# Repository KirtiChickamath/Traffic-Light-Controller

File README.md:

# Traffic-Light-Controller
Microcontroller-based traffic light controller PCB using ATmega328P, RGB LEDs, and a two-digit countdown timer with SSDs. Includes onboard 12V to 5V power regulation using LM7805. Designed as the final project for a PCB design course.

## Project Details

**Project Name:** Traffic Light Controller

**Software Used:** Eagle

## Project Description

Designed a microcontroller-based traffic signal controller PCB featuring:

- **ATmega328P** as the microcontroller
- **RGB LEDs** as traffic lights (Red, Yellow, Green)
- Two **7-segment displays (SSD)** with driver ICs to show a two-digit countdown timer
- Power supply section converting **12V DC to 5V DC** using an **LM7805 voltage regulator**
- Complete **schematic and PCB layout** created using provided component libraries

The controller manages traffic signals and displays a countdown timer to indicate the remaining time for each light.

## Block Diagram

*Block diagram showing the overall system architecture*

## Schematic

## PCB Layout

## Manufacturing Tab

## Features

- Microcontroller-controlled traffic lights using RGB LEDs
- Two-digit countdown timer visible on SSDs
- On board 12V to 5V regulated power supply using LM7805

## Tools and Components

- **Microcontroller:** ATmega328P
- **Display:** Two 7-segment displays with driver ICs
- **Traffic Light:** RGB LEDs
- **Power Supply:** LM7805 voltage regulator (12V to 5V)
- Component libraries provided by the course mentor

## Project Files

- `Schematic` — Circuit diagrams  
- `PCB Layout` — PCB design layout  
- `CAM Outputs/Gerber Files` — Manufacturing files for PCB fabrication  
- `BOM` — Bill of Materials listing all components   
- `Images` — Board photos and design previews  
- `Libraries` — Libraries were provided by mentor

## Credits

This project was developed as part of a final project of a course from [Internshala](https://internshala.com/).

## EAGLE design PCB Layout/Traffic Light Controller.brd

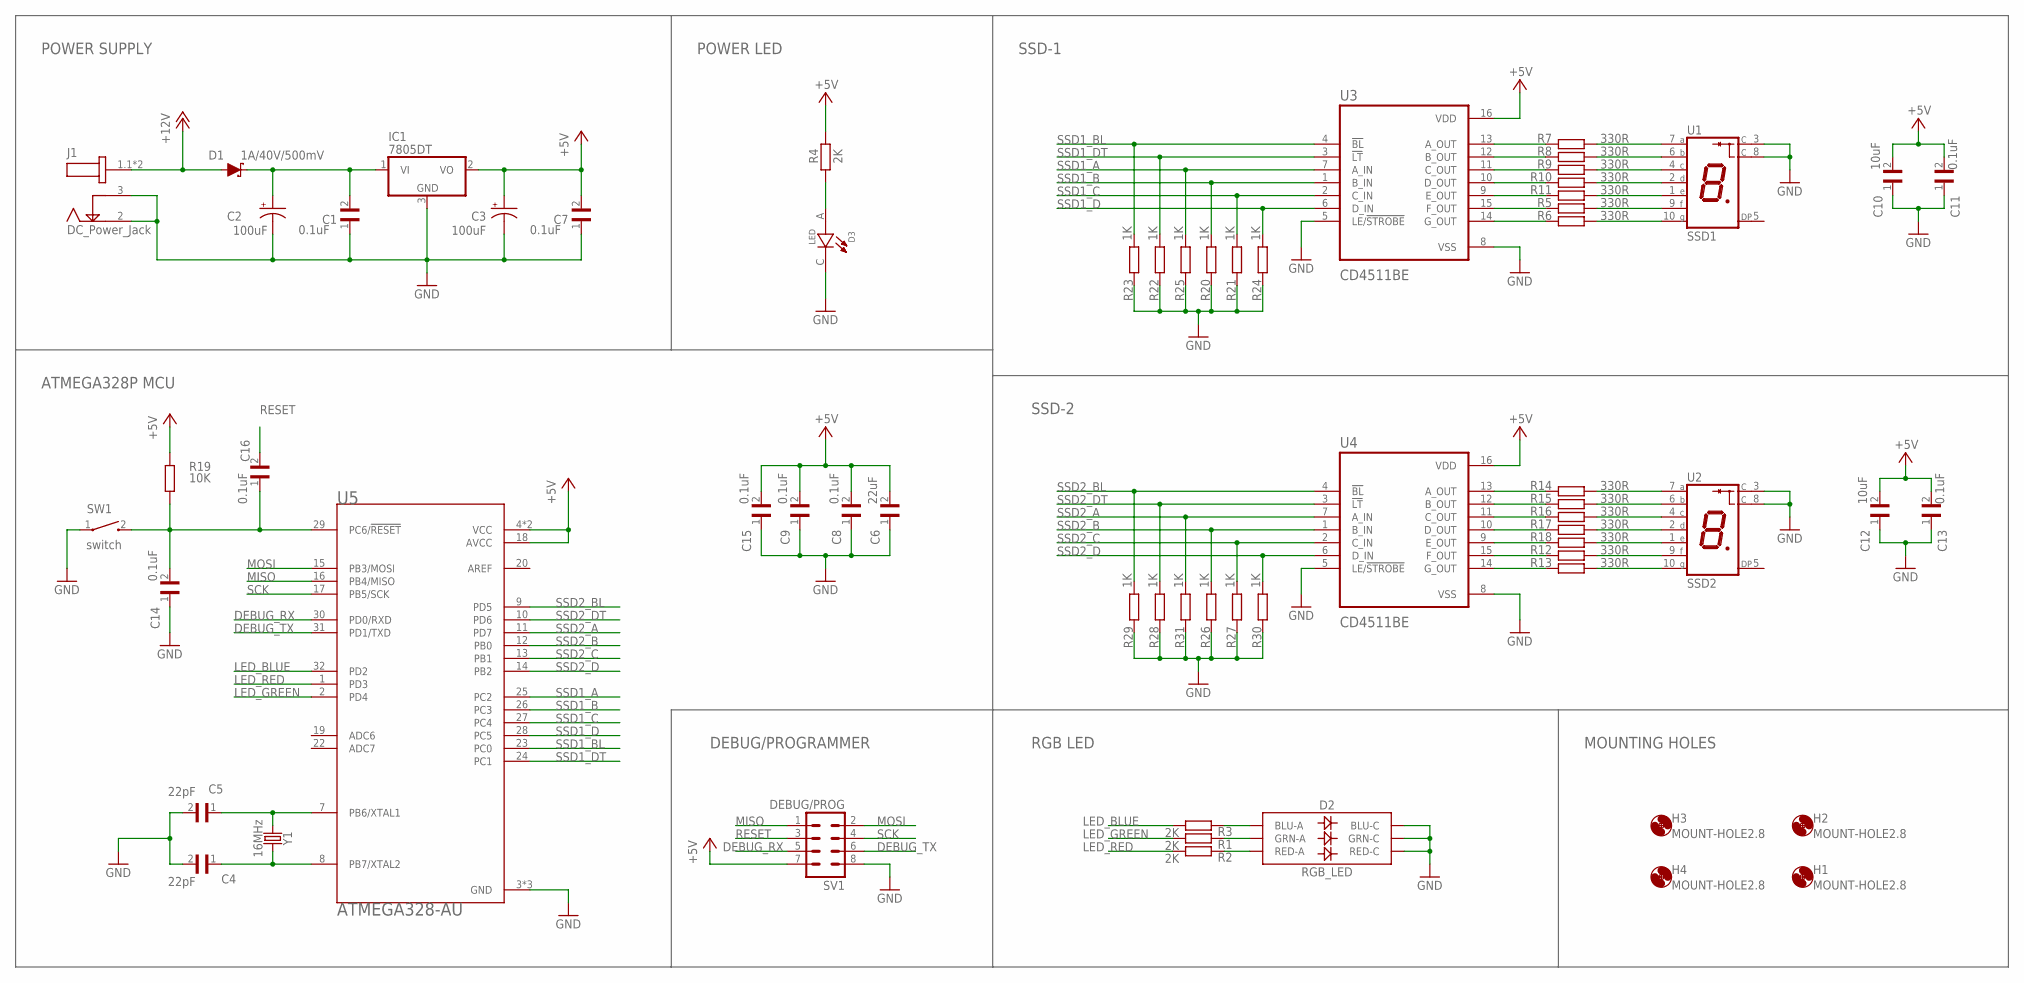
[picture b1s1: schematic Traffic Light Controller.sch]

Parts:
C1, C7, C8, C9, C11, C13, C14, C15, C16: 0.1uF; C0603
C2, C3: 100uF; CPOL-RADIAL-2.5MM-6.5MM
C4, C5: 22pF; C0603
C6: 22uF; C0603
C10, C12: 10uF; C0603
D1: 1A/40V/500mV; SMA-DIODE
D2: RGB_LED; LED-TRICOLOR-5050
D3: LED; LEDC1608X65N
H1, H2, H3, H4: MOUNT-HOLE2.8; 2,8
IC1: 7805DT; TO252
J1: DC_Power_Jack; GCT_DCJ200-05-A-XX-X_REVA
R1, R2, R3, R4: 2K; R0603
R5, R6, R7, R8, R9, R10, R11, R12, R13, R14, R15, R16, R17, R18: 330R; R0603
R19: 10K; R0603
R20, R21, R22, R23, R24, R25, R26, R27, R28, R29, R30, R31: 1K; R0603
SV1: DEBUG/PROG; MA04-2
SW1: switch; SW_1437566-3
U1: SSD1; LED_SC52-11HWA
U2: SSD2; LED_SC52-11HWA
U3, U4: CD4511BE; DIP794W45P254L1969H508Q16
U5: ATMEGA328-AU; QFP80P900X900X120-32N
Y1: 16MHz; HC49US

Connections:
+5V: C3.1 (+), C6.2, C7.2, C8.2, C9.2, C10.2, C11.2, C12.2, C13.2, C15.2, IC1.2 (VO), R4.2, R19.2, SV1.7, U3.16 (VDD), U4.16 (VDD), U5.4 (VCC), U5.6 (VCC), U5.18 (AVCC)
+12V: D1.A, J1.1.1 (1), J1.1.2 (1)
DEBUG_RX: SV1.5, U5.30 (PD0/RXD)
DEBUG_TX: SV1.6, U5.31 (PD1/TXD)
GND: C1.1, C2.2 (-), C3.2 (-), C4.2, C5.2, C6.1, C7.1, C8.1, C9.1, C10.1, C11.1, C12.1, C13.1, C14.1, C15.1, D2.4 (BLU-C), D2.5 (RED-C), D2.6 (GRN-C), D3.C, IC1.3 (GND), J1.2, J1.3, R20.2, R21.2, R22.2, R23.2, R24.2, R25.2, R26.2, R27.2, R28.2, R29.2, R30.2, R31.2, SV1.8, SW1.1, U1.3 (C), U1.8 (C), U2.3 (C), U2.8 (C), U3.5 (LE/!STROBE), U3.8 (VSS), U4.5 (LE/!STROBE), U4.8 (VSS), U5.3 (GND), U5.5 (GND), U5.21 (GND)
LED_BLUE: R3.1, U5.32 (PD2)
LED_GREEN: R1.1, U5.2 (PD4)
LED_RED: R2.1, U5.1 (PD3)
MISO: SV1.1, U5.16 (PB4/MISO)
MOSI: SV1.2, U5.15 (PB3/MOSI)
unnamed: C1.2, C2.1 (+), D1.C, IC1.1 (VI)
unnamed: D3.A, R4.1
unnamed: C5.1, U5.7 (PB6/XTAL1), Y1.1
unnamed: R7.1, U1.7 (A)
unnamed: C4.1, U5.8 (PB7/XTAL2), Y1.2
unnamed: C14.2, C16.1, R19.1, SW1.2, U5.29 (PC6/!RESET)
unnamed: R7.2, U3.13 (A_OUT)
unnamed: R8.2, U3.12 (B_OUT)
unnamed: R9.2, U3.11 (C_OUT)
unnamed: R10.2, U3.10 (D_OUT)
unnamed: R11.2, U3.9 (E_OUT)
unnamed: R5.2, U3.15 (F_OUT)
unnamed: R6.2, U3.14 (G_OUT)
unnamed: R8.1, U1.6 (B)
unnamed: R9.1, U1.4 (C)
unnamed: R10.1, U1.2 (D)
unnamed: R11.1, U1.1 (E)
unnamed: R5.1, U1.9 (F)
unnamed: R6.1, U1.10 (G)
unnamed: R14.2, U4.13 (A_OUT)
unnamed: R15.2, U4.12 (B_OUT)
unnamed: R16.2, U4.11 (C_OUT)
unnamed: R17.2, U4.10 (D_OUT)
unnamed: R18.2, U4.9 (E_OUT)
unnamed: R12.2, U4.15 (F_OUT)
unnamed: R13.2, U4.14 (G_OUT)
unnamed: R14.1, U2.7 (A)
unnamed: R15.1, U2.6 (B)
unnamed: R16.1, U2.4 (C)
unnamed: R17.1, U2.2 (D)
unnamed: R18.1, U2.1 (E)
unnamed: R12.1, U2.9 (F)
unnamed: R13.1, U2.10 (G)
unnamed: D2.3 (BLU-A), R3.2
unnamed: D2.1 (GRN-A), R1.2
unnamed: D2.2 (RED-A), R2.2
RESET: C16.2, SV1.3
SCK: SV1.4, U5.17 (PB5/SCK)
SSD1_A: R25.1, U3.7 (A_IN), U5.25 (PC2)
SSD1_B: R20.1, U3.1 (B_IN), U5.26 (PC3)
SSD1_BL: R23.1, U3.4 (!BL), U5.23 (PC0)
SSD1_C: R21.1, U3.2 (C_IN), U5.27 (PC4)
SSD1_D: R24.1, U3.6 (D_IN), U5.28 (PC5)
SSD1_DT: R22.1, U3.3 (!LT), U5.24 (PC1)
SSD2_A: R31.1, U4.7 (A_IN), U5.11 (PD7)
SSD2_B: R26.1, U4.1 (B_IN), U5.12 (PB0)
SSD2_BL: R29.1, U4.4 (!BL), U5.9 (PD5)
SSD2_C: R27.1, U4.2 (C_IN), U5.13 (PB1)
SSD2_D: R30.1, U4.6 (D_IN), U5.14 (PB2)
SSD2_DT: R28.1, U4.3 (!LT), U5.10 (PD6)

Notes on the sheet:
POWER SUPPLY
POWER LED
SSD-1
SSD-2
DEBUG/PROGRAMMER
ATMEGA328P MCU
RGB LED
MOUNTING HOLES

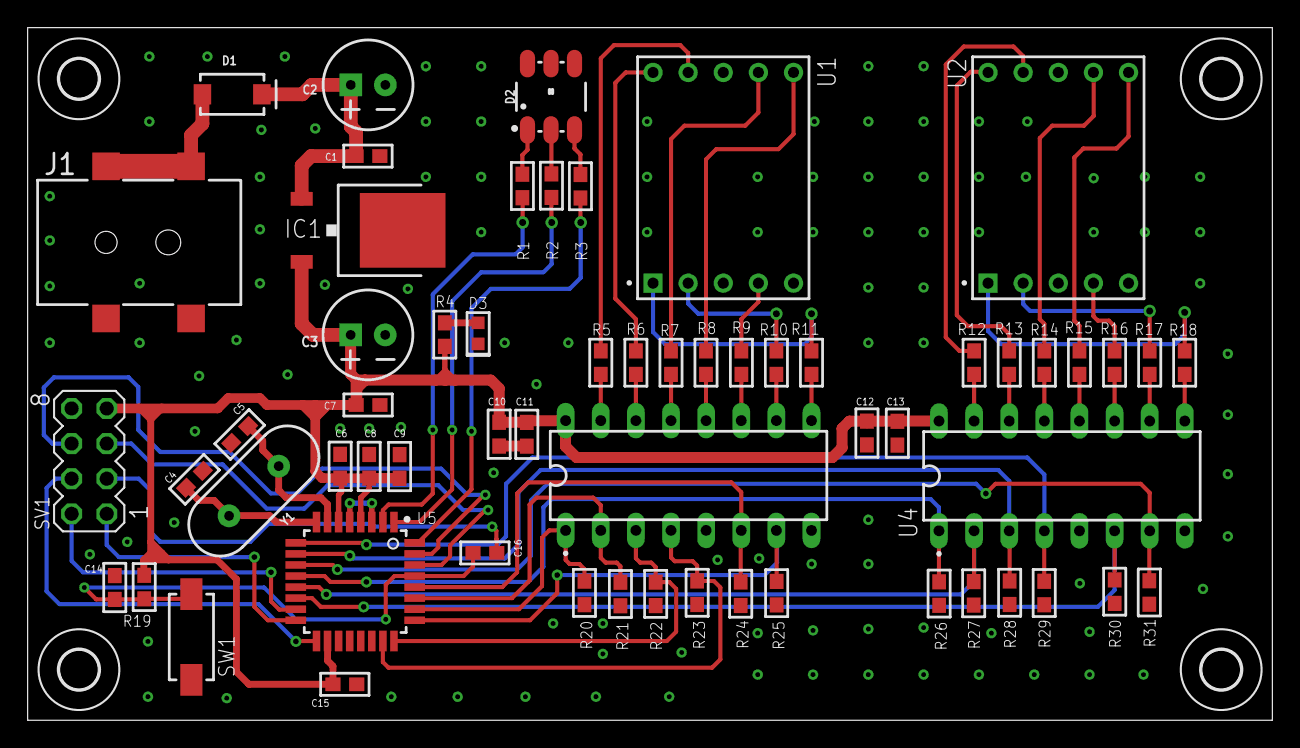
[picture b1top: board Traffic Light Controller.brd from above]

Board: 2 copper layers, 90.0 x 50.1 mm, 64 parts (0 on the bottom side), 60 nets.

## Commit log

2025-05-26 Create t
2025-05-26 README.md
